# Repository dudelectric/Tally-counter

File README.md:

# Tally-counter
3V Coin cell powered tally counter using attiny 2313 and 7 segment led

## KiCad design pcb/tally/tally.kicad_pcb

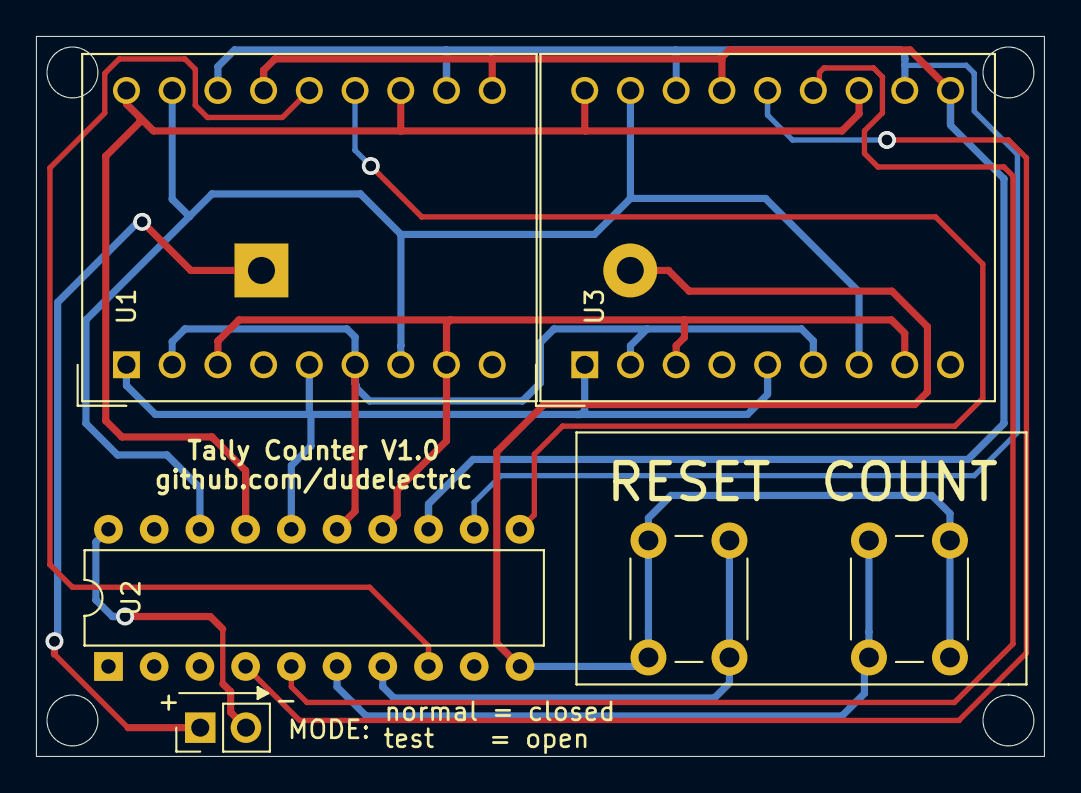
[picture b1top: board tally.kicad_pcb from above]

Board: 2 copper layers, 56.0 x 40.0 mm, 7 parts (1 on the bottom side), 16 nets.

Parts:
BT1: Battery_Cell; BatteryHolder_Keystone_103_1x20mm
COUNT: COUNT; SW_PUSH_6mm_H7.3mm
J1: Conn_01x02; PinHeader_1x02_P2.54mm_Vertical
RESET: RESET; SW_PUSH_6mm_H7.3mm
U1, U3: DA56-11GWA; DA56-11CGKWA
U2: ATtiny2313-20PU; DIP-20_W7.62mm

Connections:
GND: BT1.2, COUNT.2, RESET.2, U2.10
unnamed: BT1.1, J1.1
unnamed: J1.2, U2.20
unnamed: COUNT.1, U2.6
unnamed: RESET.1, U2.7
unnamed: U1.1, U1.5, U2.16, U3.1, U3.5
unnamed: U1.2, U1.6, U2.15, U3.2, U3.6
unnamed: U1.3, U1.8, U2.14, U3.3, U3.8
unnamed: U1.10, U1.15, U2.13, U3.10, U3.15
unnamed: U1.11, U1.16, U2.12, U3.11, U3.16
unnamed: U1.12, U1.18, U2.17, U3.12, U3.18
unnamed: U1.13, U2.11
unnamed: U1.14, U2.8
unnamed: U1.7, U1.17, U2.18, U3.7, U3.17
unnamed: U2.4, U3.14
unnamed: U2.5, U3.13

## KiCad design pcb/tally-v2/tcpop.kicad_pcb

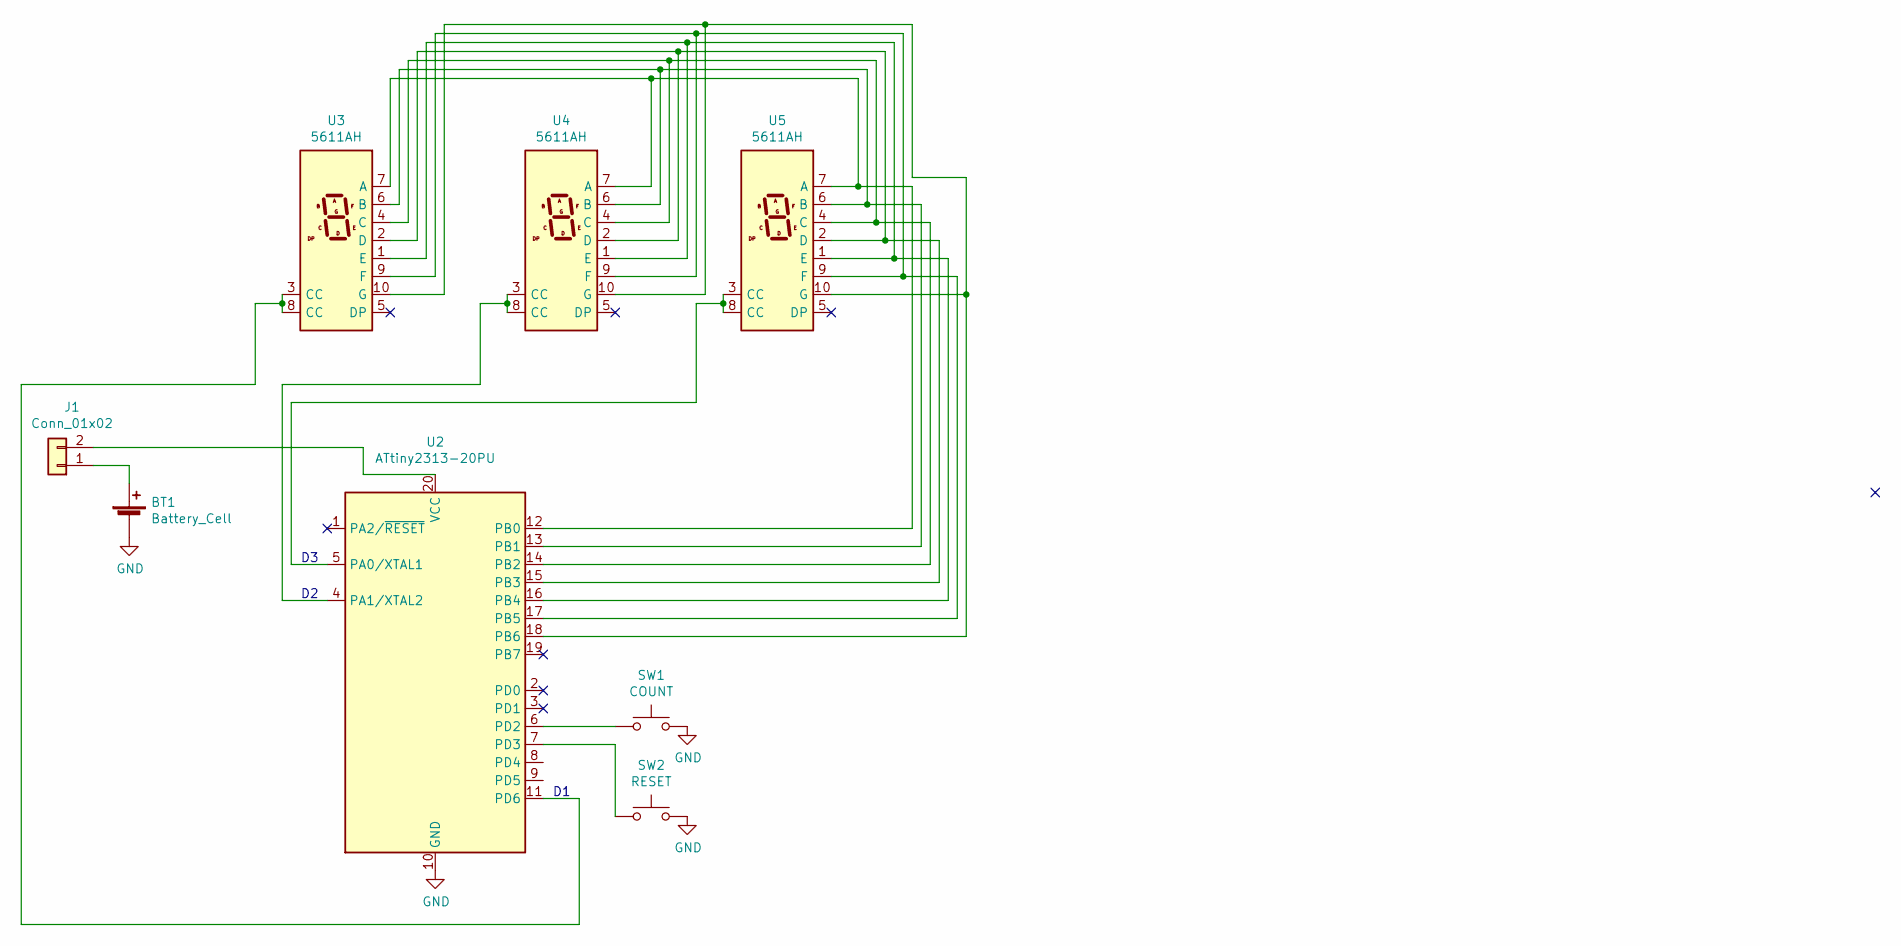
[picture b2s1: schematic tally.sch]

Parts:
BT1: Battery_Cell; BatteryHolder_Keystone_103_1x20mm
J1: Conn_01x02; PinHeader_1x02_P2.54mm_Vertical
SW1: COUNT; SW_PUSH_6mm_H7.3mm
SW2: RESET; SW_PUSH_6mm_H7.3mm
U2: ATtiny2313-20PU; DIP-20_W7.62mm
U3, U4, U5: 5611AH; 7segdisp_sa05

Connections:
GND: BT1.2 (-), SW1.2, SW2.2, U2.10 (GND)
unnamed: BT1.1 (+), J1.1
unnamed: J1.2, U2.20 (VCC)
unnamed: SW1.1, U2.6 (PD2)
unnamed: SW2.1, U2.7 (PD3)
unnamed: U2.4 (PA1/XTAL2), U4.3 (CC), U4.8 (CC)
unnamed: U2.5 (PA0/XTAL1), U5.3 (CC), U5.8 (CC)
unnamed: U2.11 (PD6), U3.3 (CC), U3.8 (CC)
unnamed: U2.12 (PB0), U3.7 (A), U4.7 (A), U5.7 (A)
unnamed: U2.13 (PB1), U3.6 (B), U4.6 (B), U5.6 (B)
unnamed: U2.14 (PB2), U3.4 (C), U4.4 (C), U5.4 (C)
unnamed: U2.15 (PB3), U3.2 (D), U4.2 (D), U5.2 (D)
unnamed: U2.16 (PB4), U3.1 (E), U4.1 (E), U5.1 (E)
unnamed: U2.17 (PB5), U3.9 (F), U4.9 (F), U5.9 (F)
unnamed: U2.18 (PB6), U3.10 (G), U4.10 (G), U5.10 (G)

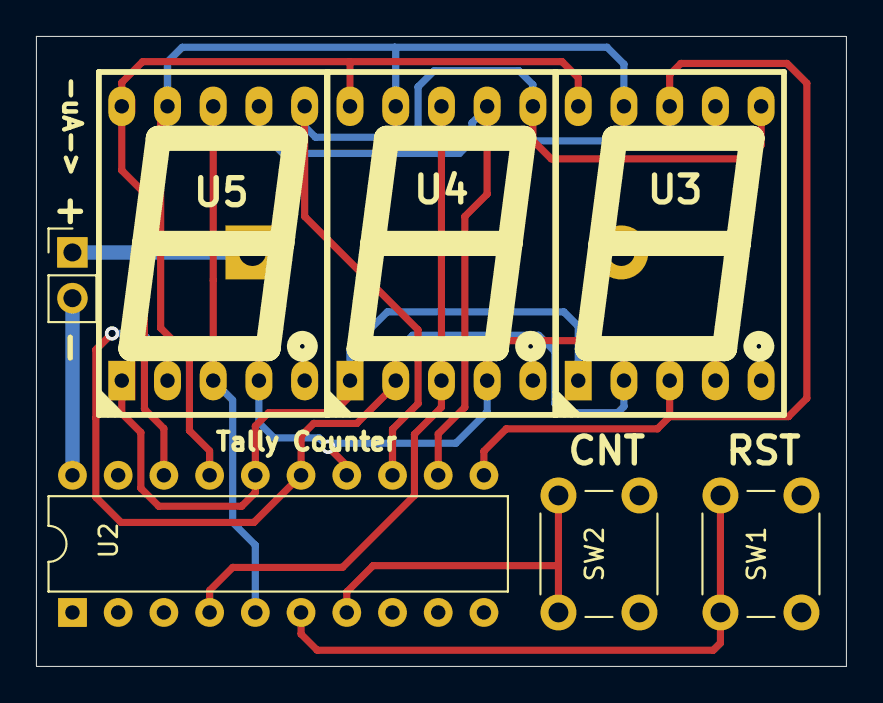
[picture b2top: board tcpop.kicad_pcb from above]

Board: 2 copper layers, 45.0 x 35.0 mm, 8 parts (1 on the bottom side), 15 nets.

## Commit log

2021-08-23 Release v1.0
2021-10-06 update pic
2021-10-06 update sch
2021-10-06 add images
